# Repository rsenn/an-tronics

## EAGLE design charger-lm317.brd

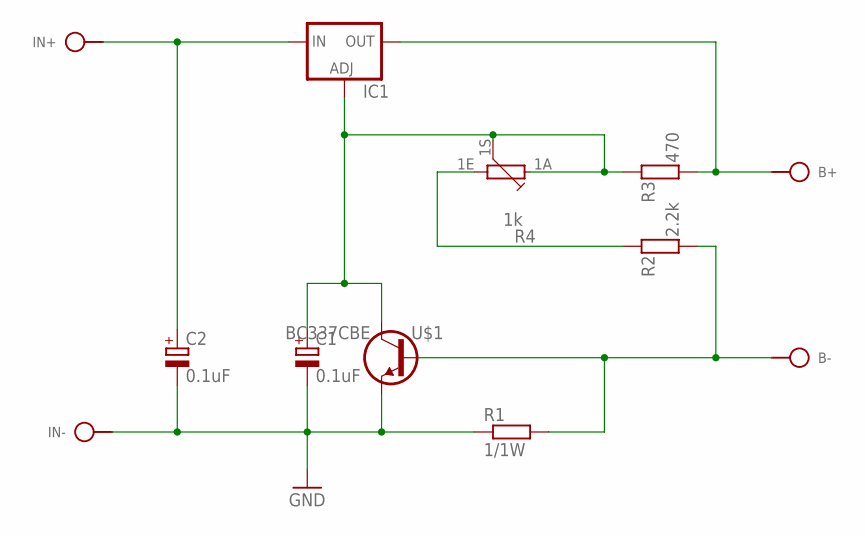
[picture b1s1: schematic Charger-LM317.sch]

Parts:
B+: SPAD
B-: SPAD
C1: 0.1uF; E5-4
C2: 0.1uF; E2,5-4
IC1: LM317TL; 317TL
IN+: SPAD
IN-: SPAD
R1: 1/1W; 0309/12
R2: 2.2k; 0204/10
R3: 470; 0204/10
R4: 1k; PC16S
U$1: BC337CBE; TO92-CBE

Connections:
GND: C1.-, C2.-, IN-.1, R1.1, U$1.E
unnamed: B-.1, R1.2, R2.1, U$1.B
unnamed: R2.2, R4.1E
unnamed: C1.+, IC1.1 (ADJ), R3.2, R4.1A, R4.1S, U$1.C
unnamed: B+.1, IC1.2 (OUT), R3.1
unnamed: C2.+, IC1.3 (IN), IN+.1

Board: 2 copper layers, 12 parts (0 on the bottom side), 6 nets, no tracks yet.

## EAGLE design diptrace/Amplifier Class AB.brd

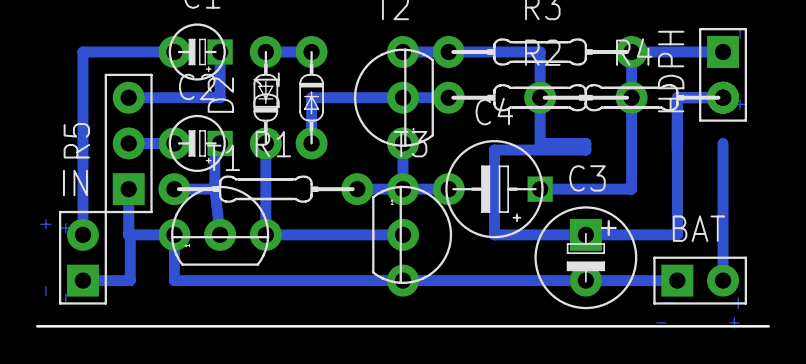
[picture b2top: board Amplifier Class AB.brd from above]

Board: 2 copper layers, 17 parts (0 on the bottom side), 12 nets.

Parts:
BAT: SPAD+-+-; SPAD+-
C1, C2: 4.7uF; E2,5-3
C3: 470uF; E2,5-6
C4: 100uF; E5-4
D1: 1N4148; DO34-5-V
D2: 1N4148; DO34-5V
HDPH: SPAD+--+; SPAD-+
IN: SPAD+--+; SPAD-+
R1: 100k; 0204/10
R2: 330; 0204/10
R3: 100; 0204/10
R4: 27; 0204/10
R5: 100k; CONN-3P
T1: 2N3904; TO92
T2: 2N3904; TO92_T2
T3: 2N3906; TO92_T2

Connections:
GND: BAT.1, C3.-, IN.1, R5.1, T1.1, T3.3
unnamed: D1.A, R2.1, T2.2
unnamed: D2.C, T1.3, T3.2
unnamed: D1.C, D2.A
unnamed: C4.-, R1.2, T2.1, T3.1
unnamed: C1.+, R5.3
unnamed: C2.-, R5.2
unnamed: C2.+, R1.1, T1.2
unnamed: R3.1, T2.3
unnamed: C4.+, HDPH.1, R2.2, R3.2
unnamed: C1.-, IN.2
NET_13: HDPH.2, R4.1

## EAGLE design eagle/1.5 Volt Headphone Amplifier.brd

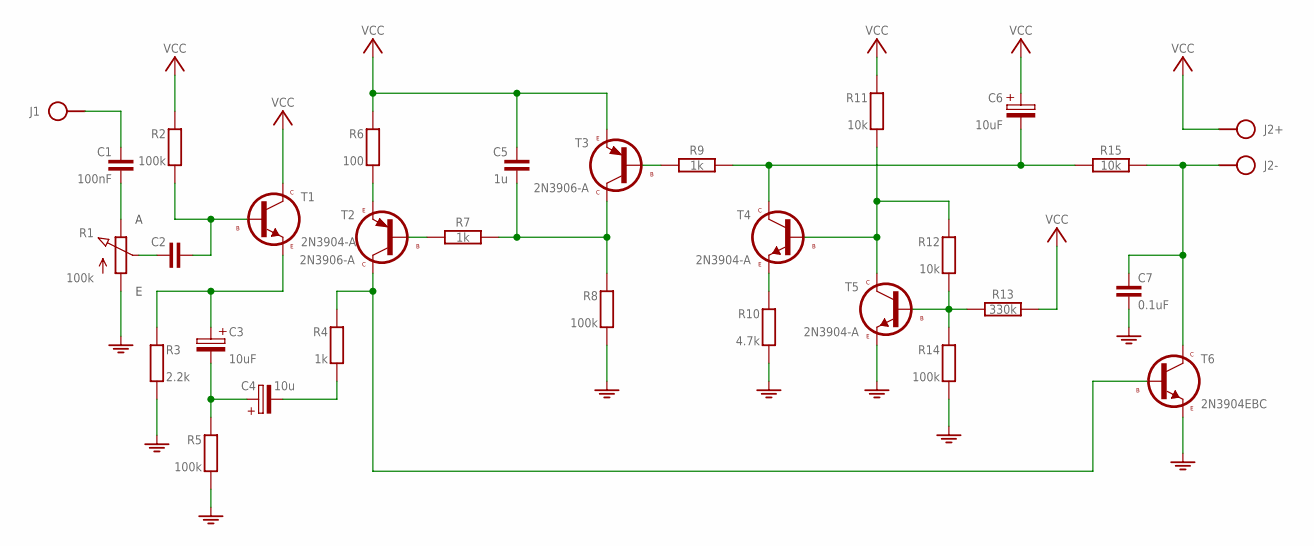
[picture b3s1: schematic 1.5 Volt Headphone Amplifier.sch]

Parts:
C1: 100nF; C050-025X075/V
C2: C-H050-025X075/V; C050-025X075/V
C3, C6: 10uF; E2,5-5
C4: 10u; E2,5-5/V
C5: 1u; C050-025X075/V
C7: 0.1uF; C050-025X075/V
J1: IN; SPAD
J2: HDPH; SPAD+-
R1: 100k; TRIM-POT
R2, R5, R8, R14: 100k; 0204/10-V
R3: 2.2k; 0204/10-V
R4: 1k; 0204/10-V
R6: 100; 0204/10-V
R7, R9: 1k; 0204/10
R10: 4.7k; 0204/10-V
R11, R12: 10k; 0204/10-V
R13: 330k; 0204/10
R15: 10k; 0204/10
T1, T4, T5: 2N3904-A; TO92-EBC-A
T2, T3: 2N3906-A; TO92-EBC-A
T6: 2N3904EBC; TO92-EBC

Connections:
GND: C7.2, R1.A, R3.2 (1), R5.2 (1), R8.2 (1), R10.2 (1), R14.2 (1), T5.E, T6.E
unnamed: C1.2, R1.E
unnamed: C2.1, R1.S
unnamed: C2.2, R2.2 (1), T1.B
unnamed: C3.+, R3.1 (2), T1.E
unnamed: C3.-, C4.+
unnamed: C4.-, R4.2 (1)
unnamed: R4.1 (2), T2.C, T6.B
unnamed: R7.1, T2.B
unnamed: R6.2 (1), T2.E
unnamed: R9.1, T3.B
unnamed: C1.1, J1.1
unnamed: C5.2, R7.2, R8.1 (2), T3.C
unnamed: R10.1 (2), T4.E
unnamed: R11.2 (1), R12.1 (2), T4.B, T5.C
unnamed: C6.-, R9.2, R15.1, T4.C
unnamed: R12.2 (1), R13.1, R14.1 (2), T5.B
unnamed: C7.1, J2.1, R15.2, T6.C
VCC: C5.1, C6.+, J2.2, R2.1 (2), R6.1 (2), R11.1 (2), R13.2, T1.C, T3.E

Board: 2 copper layers, 30 parts (0 on the bottom side), 19 nets, no tracks yet.

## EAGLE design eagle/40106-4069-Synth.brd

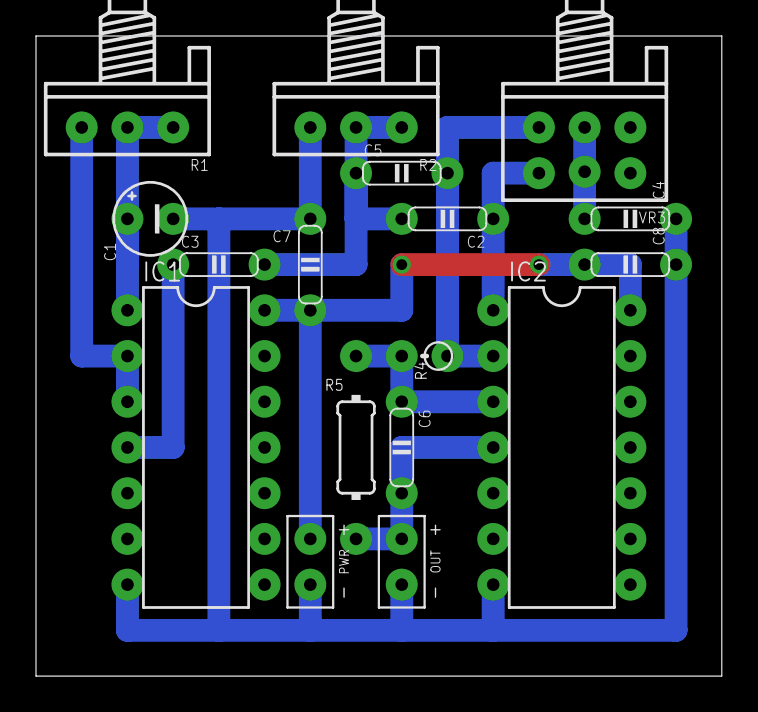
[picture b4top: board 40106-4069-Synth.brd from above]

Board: 2 copper layers, 38.1 x 35.6 mm, 17 parts (0 on the bottom side), 11 nets.

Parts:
C1: 1μF; E2.5-4/V
C2, C3, C5: 100nF; C050-020X044
C4: 220nF; C050-020X044/V
C6: 10nF; C050-020X044
C7, C8: 100nF; C050-020X044/V
IC1: 40106N; DIL14
IC2: 4069N; DIL14
OUT: SPAD+--+; SPAD+-
PWR: VCC_GNDR; SPAD+-
R1, R2: 100kΩ; POT
R4: 0202/2V
R5: 0204/10-V
VR3: 100kΩ; POT-STEREO-2X3

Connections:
GND: C1.-, C4.1, C7.1, C8.1, IC1.7, IC2.7, OUT.1, PWR.1, R2.E
unnamed: C3.1, IC1.4
unnamed: C1.+, IC1.1, R1.A, R1.S
unnamed: IC1.2, IC1.3, R1.E
unnamed: C2.2, C3.2, C5.1, R2.A, R2.S
unnamed: C5.2, IC2.2, R4.1, VR3.1-E
unnamed: C2.1, IC2.1, VR3.2-E
unnamed: C6.1, IC2.3, R4.2, R5.1
unnamed: C6.2, IC2.4, OUT.2, R5.2
unnamed: C4.2, VR3.1-S, VR3.2-S
VCC: C7.2, C8.2, IC1.14, IC2.14, PWR.2

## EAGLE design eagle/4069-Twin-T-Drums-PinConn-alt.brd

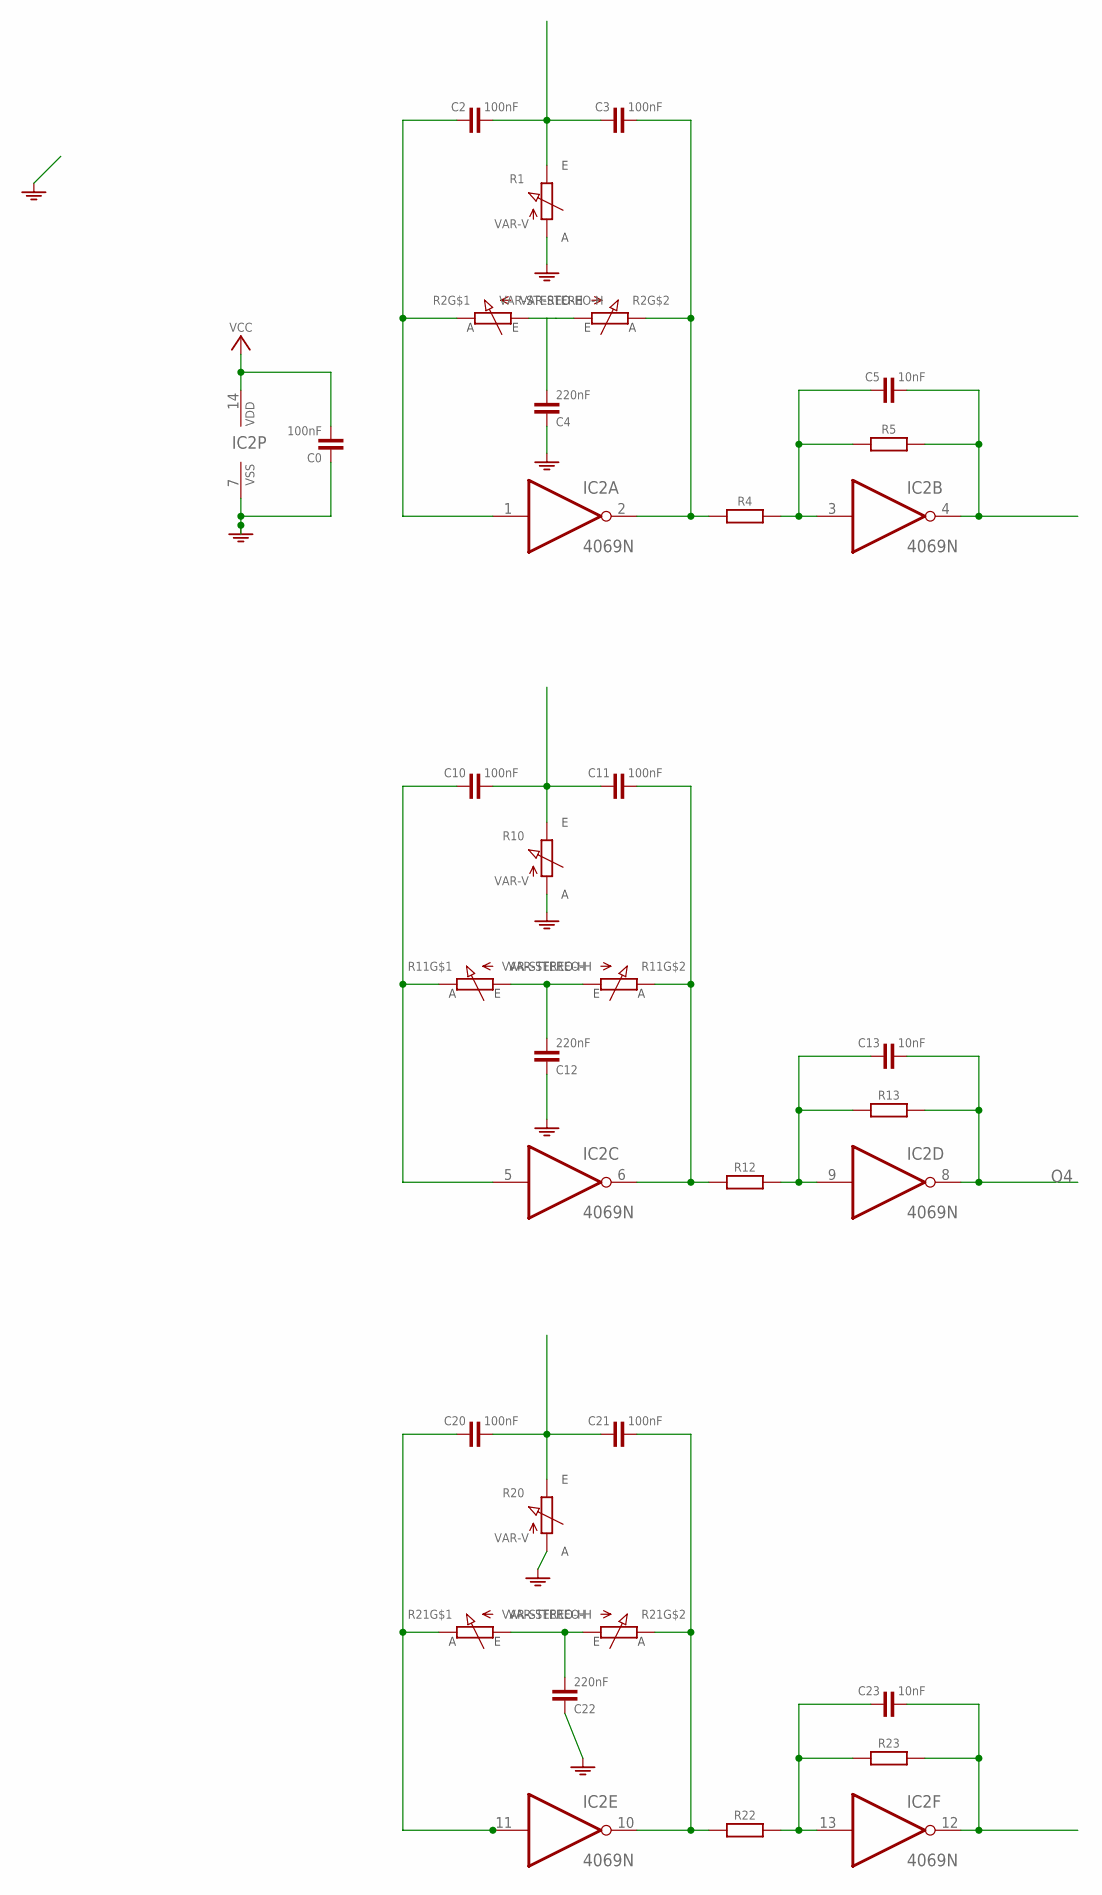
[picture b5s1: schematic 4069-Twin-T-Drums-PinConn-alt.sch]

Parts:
C0: 100nF; C050-020X044/V
C2, C3, C10, C11, C20, C21: 100nF; C050-020X044
C4, C12, C22: 220nF; C050-020X044/V
C5, C13, C23: 10nF; C025-015X024
IC2: 4069N; DIL14
R1, R10, R20: VAR-V; CONN-2P
R2, R11, R21: VAR-STEREO-H; CONN-2X2
R4, R5, R13, R23: R-H0202/2V; 0202/2V
R12: R-H0204/10; 0204/10
R22: R-H0204/10-V; 0204/10-V
S12: VCC_GNDPWR-L; PWR-L

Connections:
DR1: C4.2, R2.1 (A), R2.3 (A)
GND: C0.1, C4.1, C12.1, C22.1, IC2.7 (VSS), R1.1 (A), R10.1 (A), R20.1 (A), S12.1 (GND)
I1: C2.1, IC2.1 (I), R2.2 (S-A)
I2: C5.1, IC2.3 (I), R4.2, R5.1
I3: C10.1, IC2.5 (I), R11.2 (S-A)
I4: C13.1, IC2.9 (I), R12.2, R13.1
I5: C20.1, IC2.11 (I), R21.2 (S-A)
I6: C23.1, IC2.13 (I), R22.2, R23.1
unnamed: C12.2, R11.1 (A), R11.3 (A)
unnamed: C22.2, R21.1 (A), R21.3 (A)
O1: C3.2, IC2.2 (O), R2.4 (S-A), R4.1
O2: C5.2, IC2.4 (O), R5.2
O3: C11.2, IC2.6 (O), R11.4 (S-A), R12.1
O4: C13.2, IC2.8 (O), R13.2
O5: C21.2, IC2.10 (O), R21.4 (S-A), R22.1
O6: C23.2, IC2.12 (O), R23.2
TR1: C2.2, C3.1, R1.2 (S-E)
TR2: C10.2, C11.1, R10.2 (S-E)
TR3: C20.2, C21.1, R20.2 (S-E)
VCC: C0.2, IC2.14 (VDD), S12.2 (VCC)

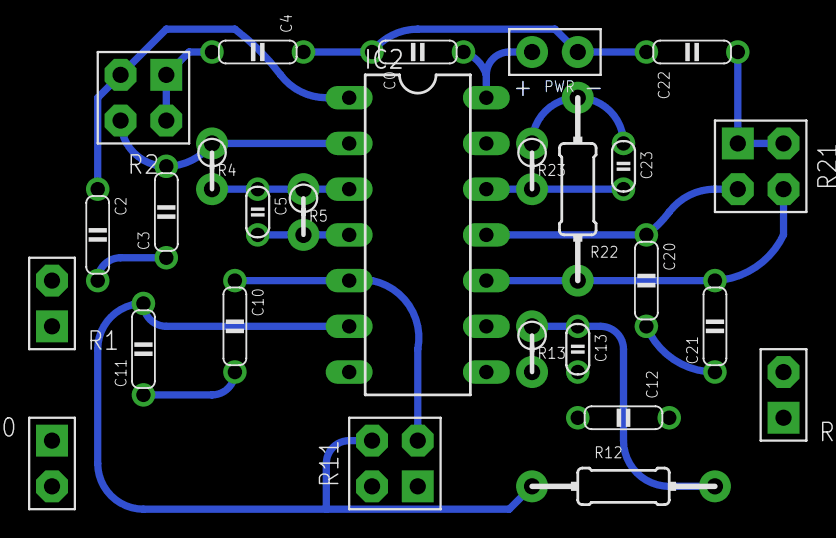
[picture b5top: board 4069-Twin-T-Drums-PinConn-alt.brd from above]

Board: 2 copper layers, 27 parts (0 on the bottom side), 20 nets.

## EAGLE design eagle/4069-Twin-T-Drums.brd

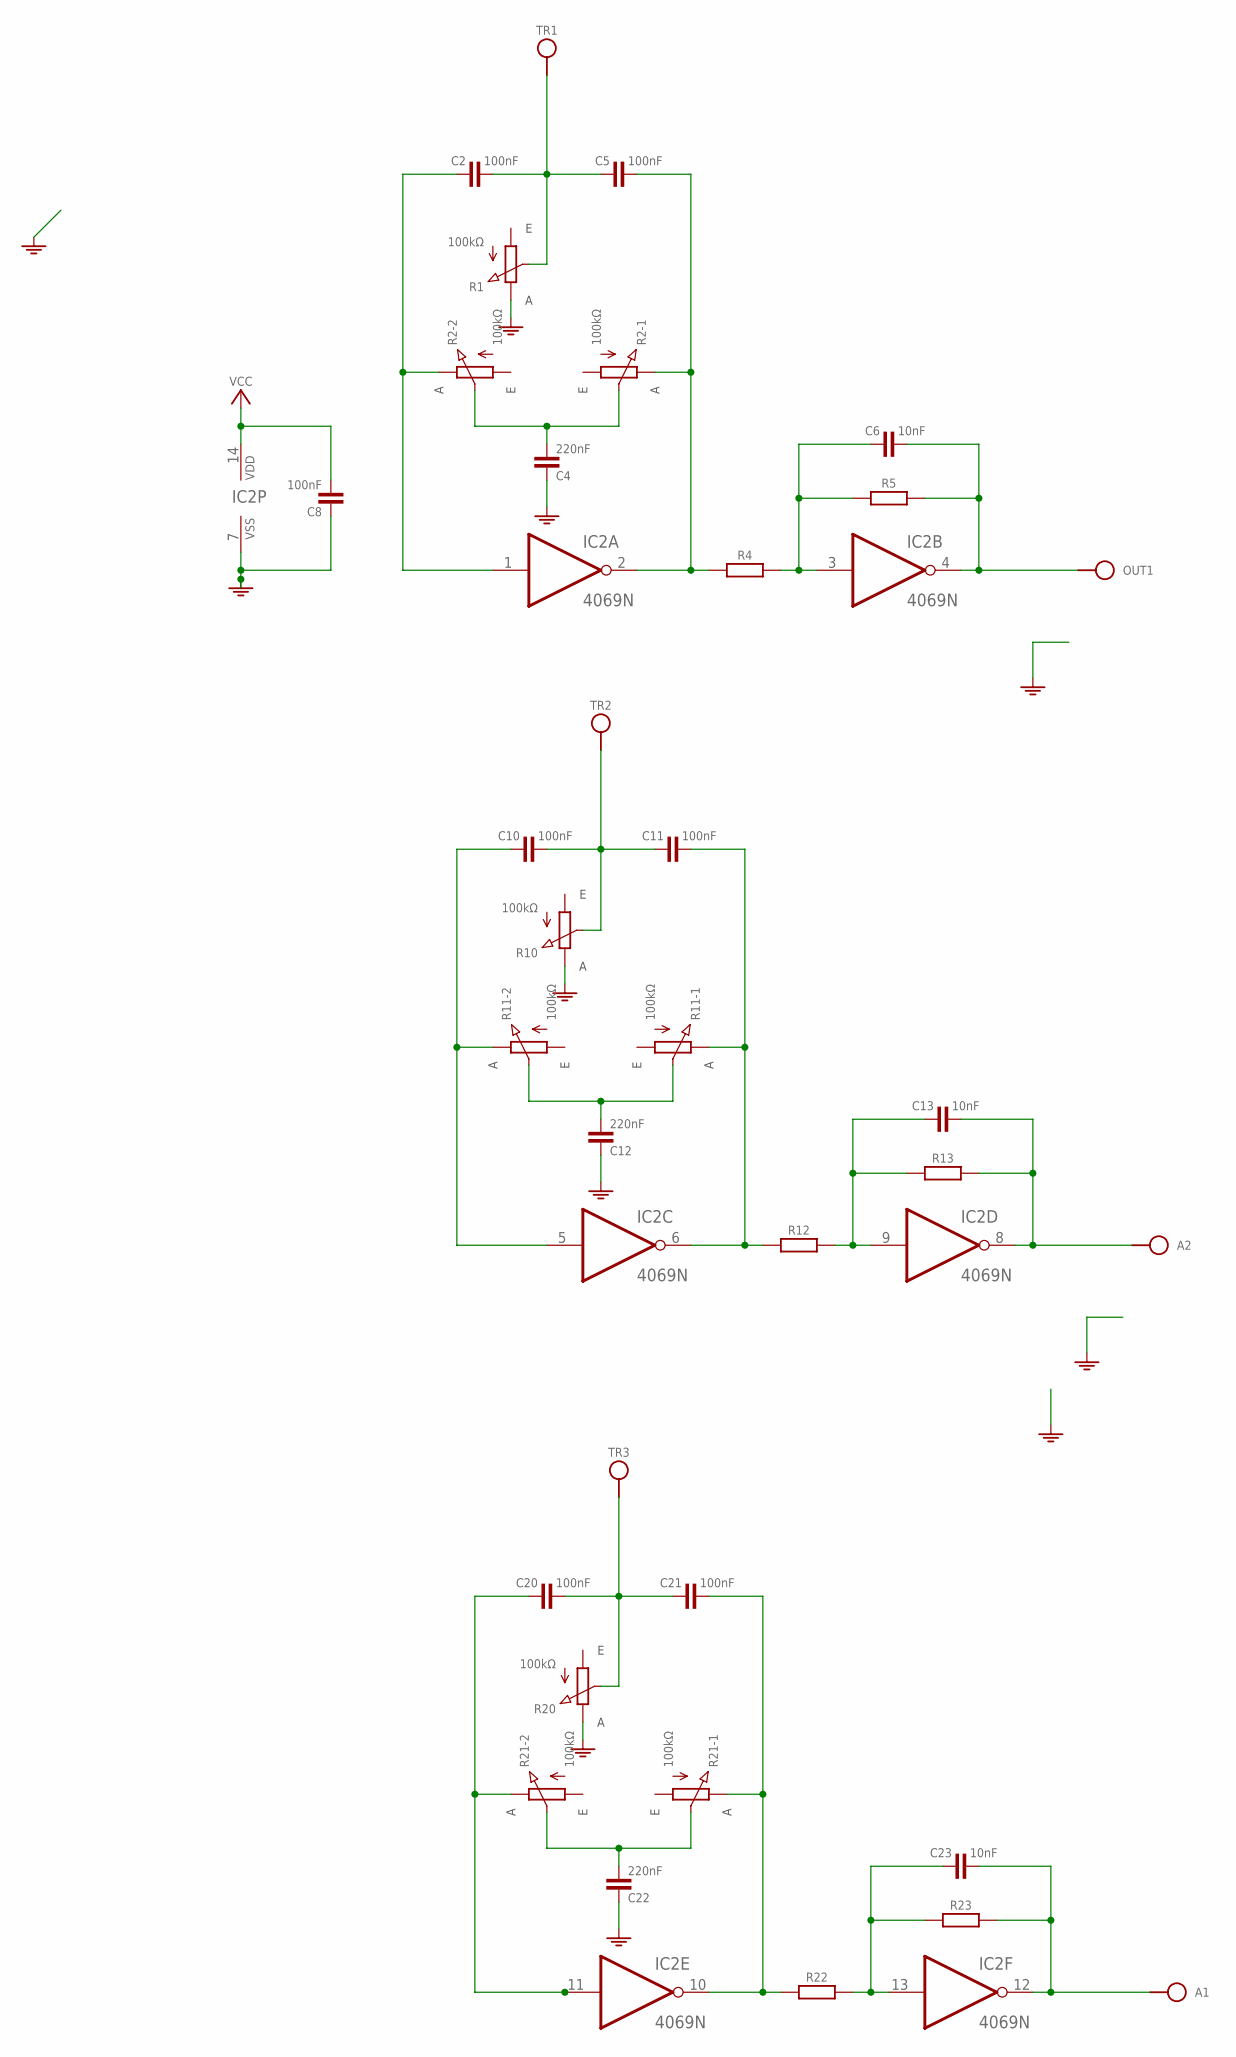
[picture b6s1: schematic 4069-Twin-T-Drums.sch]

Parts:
A1, A2: HPORT; SPAD
C2, C5, C10, C11, C20, C21: 100nF; C050-020X044
C4, C12, C22: 220nF; C050-020X044/V
C6, C13, C23: 10nF; C025-015X024
C8: 100nF; C050-020X044/V
IC2: 4069N; DIL14
OUT1: HPORT; SPAD
R1, R10, R20: 100kΩ; POT
R2, R11, R21: 100kΩ; POT-STEREO-2X3
R4, R5, R13, R22, R23: R-H0202/2V; 0202/2V
R12: R-H0202/2; 0202/2
S12: VCC_GNDPWR-L; PWR-L
TR1, TR2, TR3: VPORT; SPAD

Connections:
DR1: C4.2, R2.1-S (S), R2.2-S (S)
DR2: C12.2, R11.1-S (S), R11.2-S (S)
DR3: C22.2, R21.1-S (S), R21.2-S (S)
GND: C4.1, C8.1, C12.1, C22.1, IC2.7 (VSS), R1.E, R10.E, R20.E, S12.1 (GND)
I1: C2.1, IC2.1 (I), R2.2-E (E)
I2: C6.1, IC2.3 (I), R4.2, R5.1
I3: C10.1, IC2.5 (I), R11.2-E (E)
I4: C13.1, IC2.9 (I), R12.2, R13.1
I5: C20.1, IC2.11 (I), R21.2-E (E)
I6: C23.1, IC2.13 (I), R22.2, R23.1
O1: C5.2, IC2.2 (O), R2.1-E (E), R4.1
O2: C6.2, IC2.4 (O), OUT1.1, R5.2
O3: C11.2, IC2.6 (O), R11.1-E (E), R12.1
O4: A2.1, C13.2, IC2.8 (O), R13.2
O5: C21.2, IC2.10 (O), R21.1-E (E), R22.1
O6: A1.1, C23.2, IC2.12 (O), R23.2
TR1: C2.2, C5.1, R1.S, TR1.1
TR2: C10.2, C11.1, R10.S, TR2.1
TR3: C20.2, C21.1, R20.S, TR3.1
VCC: C8.2, IC2.14 (VDD), S12.2 (VCC)

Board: 2 copper layers, 33 parts (0 on the bottom side), 20 nets, no tracks yet.
